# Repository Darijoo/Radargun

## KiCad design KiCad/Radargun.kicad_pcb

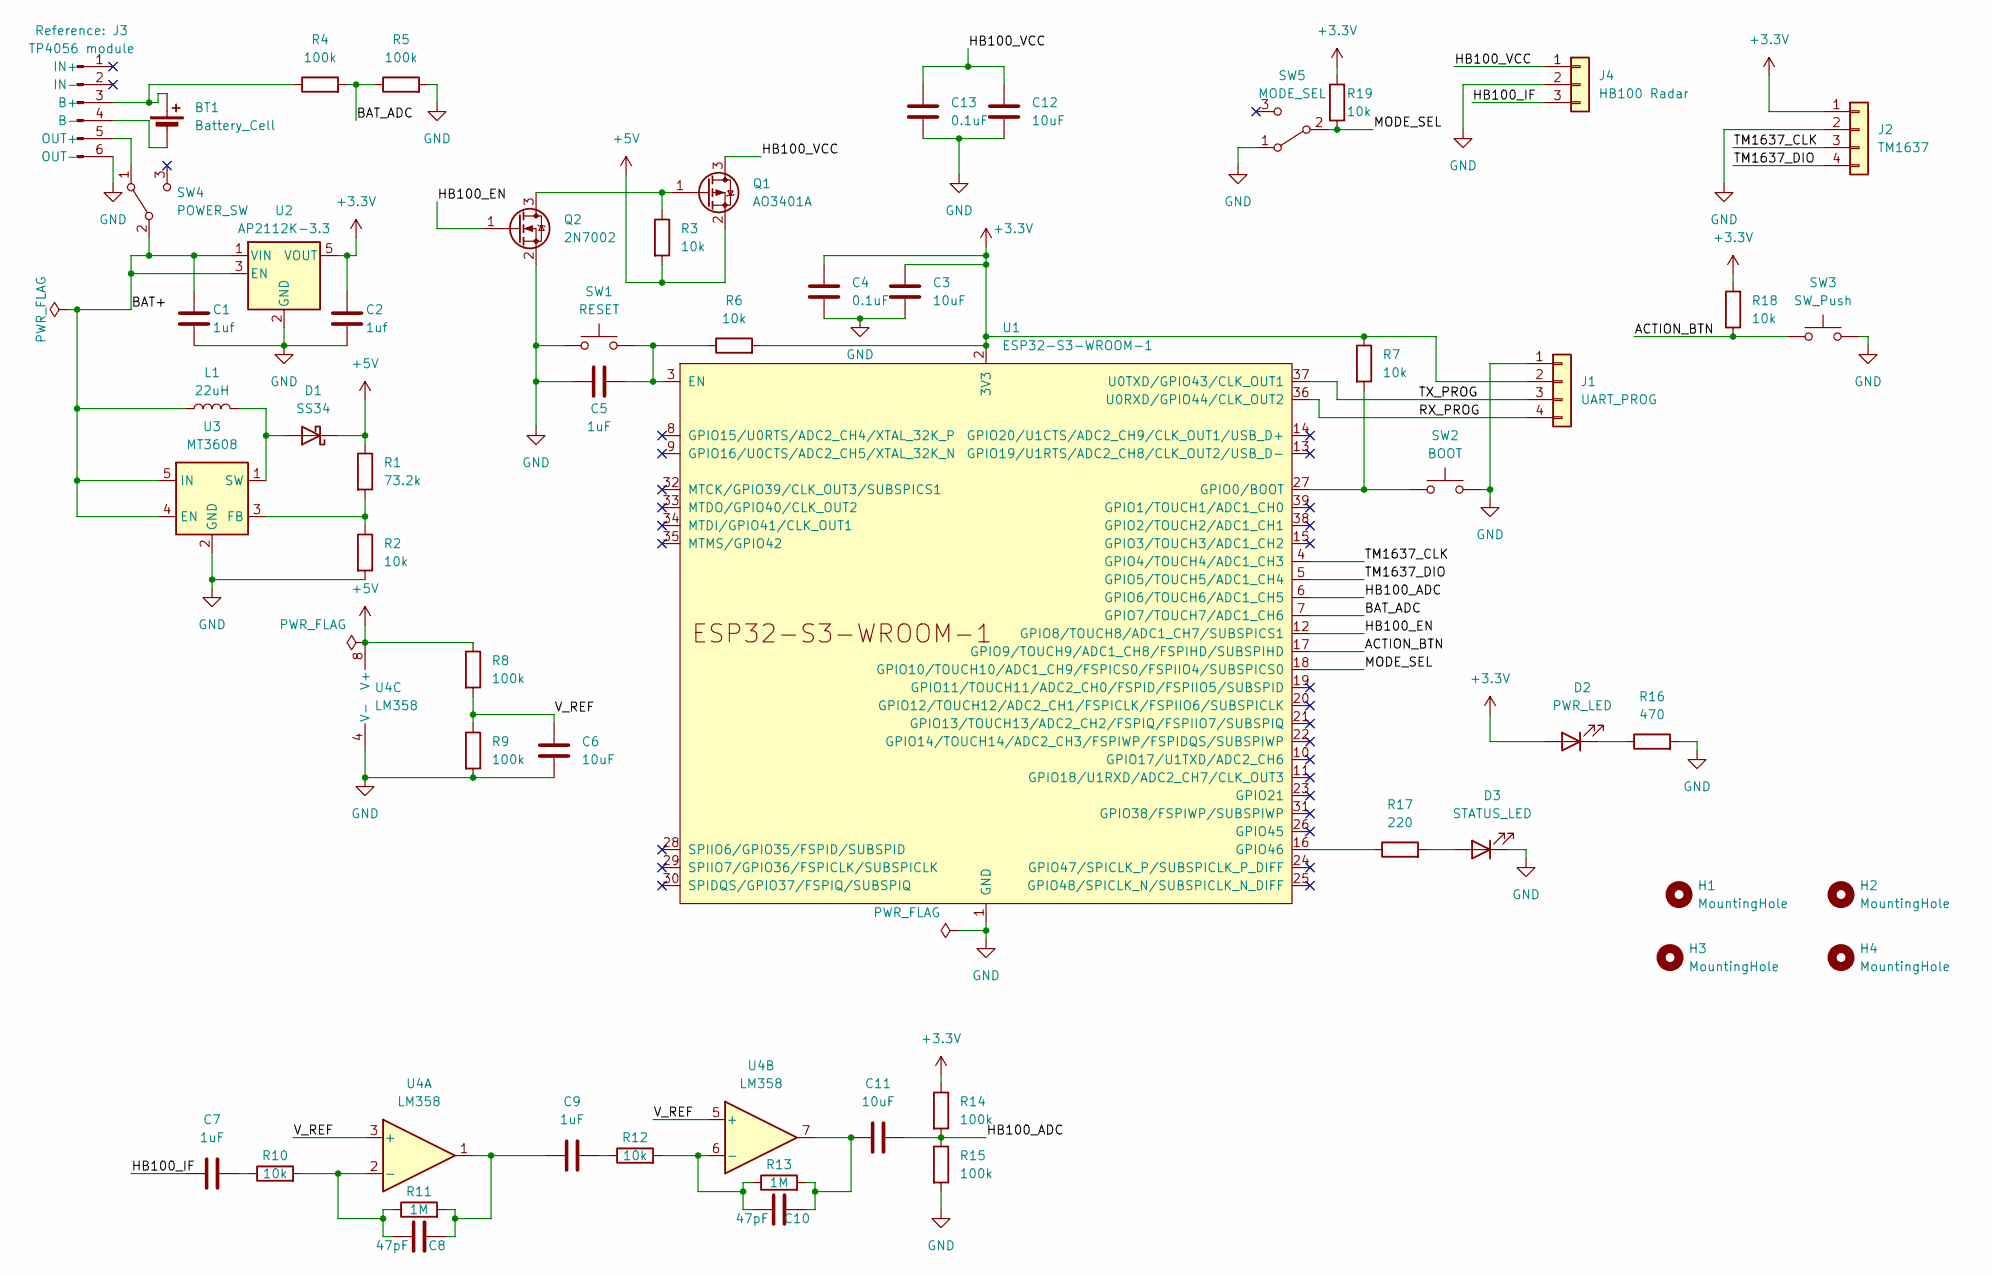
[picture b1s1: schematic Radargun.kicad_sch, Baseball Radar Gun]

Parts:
BT1: Battery_Cell; JST_PH_B2B-PH-K_1x02_P2.00mm_Vertical
C1, C2: 1uf; C_0805_2012Metric_Pad1.18x1.45mm_HandSolder
C3, C6, C11, C12: 10uF; C_0805_2012Metric_Pad1.18x1.45mm_HandSolder
C4, C13: 0.1uF; C_0805_2012Metric_Pad1.18x1.45mm_HandSolder
C5, C7, C9: 1uF; C_0805_2012Metric_Pad1.18x1.45mm_HandSolder
C8, C10: 47pF; C_0805_2012Metric_Pad1.18x1.45mm_HandSolder
D1: SS34; D_SMA
D2: PWR_LED; LED_0805_2012Metric_Pad1.15x1.40mm_HandSolder
D3: STATUS_LED; LED_0805_2012Metric_Pad1.15x1.40mm_HandSolder
H1, H2, H3, H4: MountingHole; MountingHole_3.2mm_M3
J1: UART_PROG; PinHeader_1x04_P2.54mm_Vertical
J2: TM1637; PinHeader_1x04_P2.54mm_Vertical
J3: TP4056 module; PinHeader_1x06_P2.54mm_Vertical
J4: HB100 Radar; PinHeader_1x03_P2.54mm_Vertical
L1: 22uH; L_1210_3225Metric_Pad1.42x2.65mm_HandSolder
Q1: AO3401A; SOT-23
Q2: 2N7002; SOT-23
R1: 73.2k; R_0805_2012Metric_Pad1.20x1.40mm_HandSolder
R2, R3, R6, R7, R10, R12, R18, R19: 10k; R_0805_2012Metric_Pad1.20x1.40mm_HandSolder
R4, R5, R8, R9, R14, R15: 100k; R_0805_2012Metric_Pad1.20x1.40mm_HandSolder
R11, R13: 1M; R_0805_2012Metric_Pad1.20x1.40mm_HandSolder
R16: 470; R_0805_2012Metric_Pad1.20x1.40mm_HandSolder
R17: 220; R_0805_2012Metric_Pad1.20x1.40mm_HandSolder
SW1: RESET; SW_PUSH_6mm
SW2: BOOT; SW_PUSH_6mm
SW3: SW_Push; SW_PUSH_6mm
SW4: POWER_SW; SS12D00
SW5: MODE_SEL; SS12D00
U1: ESP32-S3-WROOM-1
U2: AP2112K-3.3; SOT-23-5
U3: MT3608; SOT-23-6
U4: LM358; SOIC-8_3.9x4.9mm_P1.27mm

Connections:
+3.3V: C2.1, C3.1, C4.1, D2.2 (A), J1.2, J2.1, R6.2, R7.1, R14.1, R18.2, R19.2, U1.2 (3V3), U2.5 (VOUT)
+5V: D1.1 (K), Q1.2 (S), R1.1, R3.2, R8.1, U4.8 (V+)
/ACTION_BTN: R18.1, SW3.1, U1.17 (GPIO9/TOUCH9/ADC1_CH8/FSPIHD/SUBSPIHD)
/BAT+: C1.1, L1.1, SW4.2 (B), U2.1 (VIN), U2.3 (EN), U3.4 (EN), U3.5 (IN)
/BAT_ADC: R4.2, R5.1, U1.7 (GPIO7/TOUCH7/ADC1_CH6)
/HB100_ADC: C11.2, R14.2, R15.1, U1.6 (GPIO6/TOUCH6/ADC1_CH5)
/HB100_EN: Q2.1 (G), U1.12 (GPIO8/TOUCH8/ADC1_CH7/SUBSPICS1)
/HB100_IF: C7.1, J4.3
/HB100_VCC: C12.1, C13.1, J4.1, Q1.3 (D)
/MODE_SEL: R19.1, SW5.2 (B), U1.18 (GPIO10/TOUCH10/ADC1_CH9/FSPICS0/FSPIIO4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)
/RX_PROG: J1.4, U1.36 (U0RXD/GPIO44/CLK_OUT2)
/TM1637_CLK: J2.3, U1.4 (GPIO4/TOUCH4/ADC1_CH3)
/TM1637_DIO: J2.4, U1.5 (GPIO5/TOUCH5/ADC1_CH4)
/TX_PROG: J1.3, U1.37 (U0TXD/GPIO43/CLK_OUT1)
/V_REF: C6.1, R8.2, R9.1, U4.3 (+), U4.5 (+)
GND: C1.2, C2.2, C3.2, C4.2, C5.1, C6.2, C12.2, C13.2, D3.1 (K), J1.1, J2.2, J3.6 (OUT-), J4.2, Q2.2 (S), R2.2, R5.2, R9.2, R15.2, R16.2, SW1.1, SW2.2, SW3.2, SW5.1 (A), U1.1 (GND), U1.40 (GND), U1.41 (GND), U2.2 (GND), U3.2 (GND), U4.4 (V-)
unnamed: BT1.1 (+), J3.3 (B+), R4.1
unnamed: BT1.2 (-), J3.4 (B-)
unnamed: C7.2, R10.1
unnamed: C8.2, C9.1, R11.2, U4.1
unnamed: C9.2, R12.1
unnamed: C10.2, C11.1, R13.2, U4.7
unnamed: D1.2 (A), L1.2, U3.1 (SW)
unnamed: D2.1 (K), R16.1
unnamed: D3.2 (A), R17.2
unnamed: J3.5 (OUT+), SW4.1 (A)
unnamed: Q1.1 (G), Q2.3 (D), R3.1
unnamed: C5.2, R6.1, SW1.2, U1.3 (EN)
unnamed: R7.2, SW2.1, U1.27 (GPIO0/BOOT)
unnamed: R17.1, U1.16 (GPIO46)
unnamed: R1.2, R2.1, U3.3 (FB)
unnamed: C8.1, R10.2, R11.1, U4.2 (-)
unnamed: C10.1, R12.2, R13.1, U4.6 (-)

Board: 2 copper layers, 56 parts (0 on the bottom side), 33 nets, no tracks yet.

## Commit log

2026-06-03 Initial project setup
2026-06-03 Update BOM and Pinout for Power Management block
2026-06-03 Update BOM and Pinouts for ESP32 Core block
2026-06-03 Fix ESP32 physical pin numbers to GPIO names
2026-06-03 Update BOM and Pinouts for LM358 Analog Front-End
2026-06-04 Add UI Block and mark Phase 1 Complete
2026-06-04 Complete Phase 1 Schematic Capture (No ERC errors)
2026-06-04 Add final pre-flight safety net components and switches
2026-06-05 Add safety net components to KiCad schematic
2026-06-10 Orderlist completed.
2026-06-10 Start design PCB Layout
2026-06-17 PCB layout guide added
2026-06-18 PCB placement update
